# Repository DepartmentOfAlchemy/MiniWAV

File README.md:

# MiniWAV

The MiniWAV is a [FeatherWing](https://learn.adafruit.com/adafruit-feather/featherwings) designed for the [Feather](https://learn.adafruit.com/adafruit-feather) ecosystem create by [Adafruit](https://www.adafruit.com). It provides an SD card reader and I2S audio output to an 1/8" jack stereo audio line output. The board is designed to be used in a haunted attraction prop control system.

## Pinout
- I2S
  - BCK: A0
  - LRCK: A1
  - DIN: A2
- SD Card SPI
  - SCLK: SCK
  - DI: MO
  - DO: MI
  - CS: D10
  - DAT2: D9
  - DAT1: D6
  - CARDDET: D5

### SD Card
| Feather Pin | SPI     | SDIO    |
|-------------|---------|---------|
| SCK         | SCLK    | CLK     |
| MO          | SI      | CMD     |
| MI          | SO      | D0      |
| D10         | CS      | D3      |
| D9          | DAT2    | D2      |
| D6          | DAT1    | D1      |
| D5          | CARDDET | CARDDET |

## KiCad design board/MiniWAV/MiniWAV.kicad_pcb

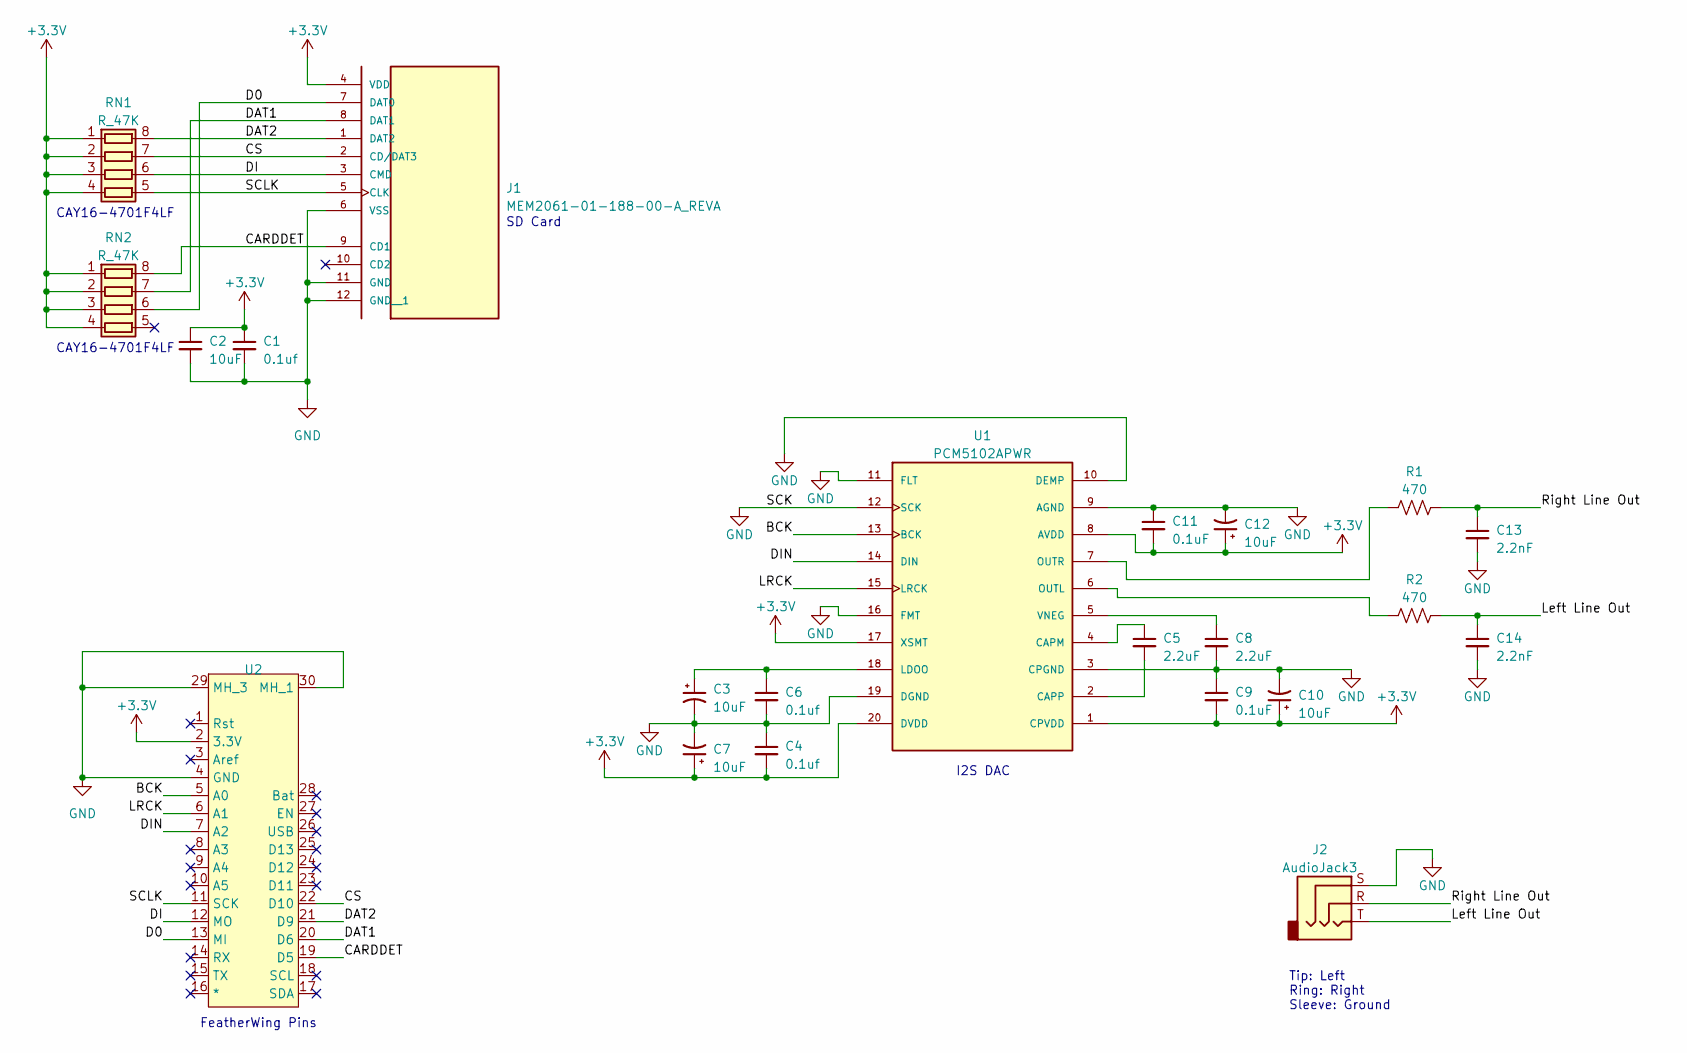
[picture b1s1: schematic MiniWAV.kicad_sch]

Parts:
C1, C4, C6: 0.1uf; C_0603_1608Metric
C2: 10uF; C_0603_1608Metric
C3, C7, C10, C12: 10uF; CAPPM2012X120N
C5, C8: 2.2uF; C_0603_1608Metric
C9, C11: 0.1uF; C_0603_1608Metric
C13, C14: 2.2nF; C_0603_1608Metric
J1: MEM2061-01-188-00-A_REVA; GCT_MEM2061-01-188-00-A_REVA
J2: AudioJack3; Jack_3.5mm_CUI_SJ-3523-SMT_Horizontal
R1, R2: 470; R_0603_1608Metric
RN1, RN2: R_47K; R_Array_Convex_4x0603
U1: PCM5102APWR; SOP65P640X120-20N; PARTREV C
U2: Feather Pins

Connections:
+3.3V: C1.1, C2.1, C4.2, C7.1, C9.2, C10.1, C11.2, C12.1, J1.4 (VDD), RN1.1 (R1.1), RN1.2 (R2.1), RN1.3 (R3.1), RN1.4 (R4.1), RN2.1 (R1.1), RN2.2 (R2.1), RN2.3 (R3.1), RN2.4 (R4.1), U1.1 (CPVDD), U1.8 (AVDD), U1.17 (XSMT), U1.20 (DVDD), U2.2 (3.3V)
/BCK: U1.13 (BCK), U2.5 (A0)
/CARDDET: J1.9 (CD1), RN2.8 (R1.2), U2.19 (D5)
/CS: J1.2 (CD/DAT3), RN1.7 (R2.2), U2.22 (D10)
/D0: J1.7 (DAT0), RN2.6 (R3.2), U2.13 (MI)
/DAT1: J1.8 (DAT1), RN2.7 (R2.2), U2.20 (D6)
/DAT2: J1.1 (DAT2), RN1.8 (R1.2), U2.21 (D9)
/DI: J1.3 (CMD), RN1.6 (R3.2), U2.12 (MO)
/DIN: U1.14 (DIN), U2.7 (A2)
/LRCK: U1.15 (LRCK), U2.6 (A1)
/Left Line Out: C14.1, J2.T, R2.2
/Right Line Out: C13.1, J2.R, R1.2
/SCLK: J1.5 (CLK), RN1.5 (R4.2), U2.11 (SCK)
GND: C1.2, C2.2, C3.2, C4.1, C6.2, C7.2, C8.2, C9.1, C10.2, C11.1, C12.2, C13.2, C14.2, J1.6 (VSS), J1.11 (GND), J1.12 (GND__1), J2.S, U1.3 (CPGND), U1.9 (AGND), U1.10 (DEMP), U1.11 (FLT), U1.12 (SCK), U1.16 (FMT), U1.19 (DGND), U2.4 (GND), U2.29 (MH_3), U2.30 (MH_1)
unnamed: C5.1, U1.4 (CAPM)
unnamed: C5.2, U1.2 (CAPP)
unnamed: C3.1, C6.1, U1.18 (LDOO)
unnamed: R2.1, U1.6 (OUTL)
unnamed: R1.1, U1.7 (OUTR)
unnamed: C8.1, U1.5 (VNEG)

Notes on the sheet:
SD Card
I2S DAC
FeatherWing Pins
CAY16-4701F4LF
Tip: Left Ring: Right Sleeve: Ground

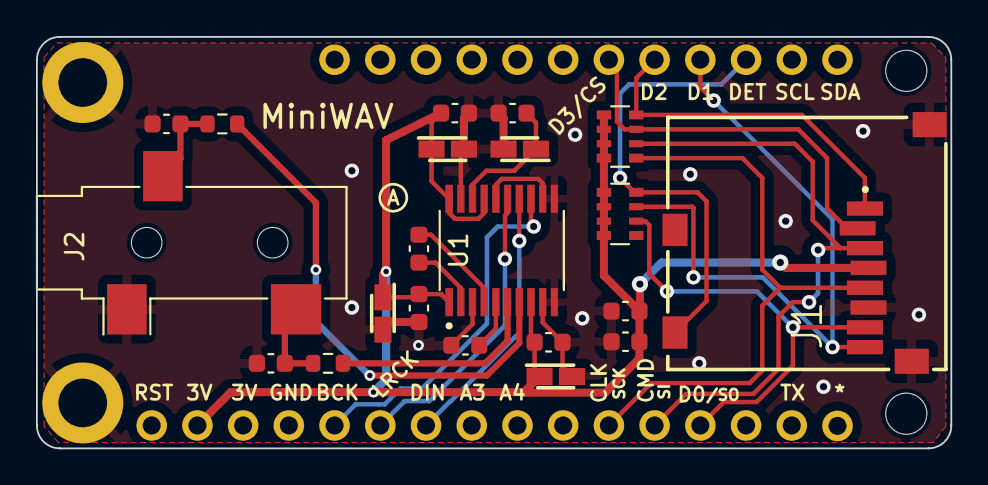
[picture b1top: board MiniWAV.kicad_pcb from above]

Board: 2 copper layers, 50.8 x 22.9 mm, 22 parts (0 on the bottom side), 20 nets.

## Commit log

2023-12-16 Initial commit.
2023-12-16 Update README.md
    Basic description of the board and pinout.
2024-07-14 Added the SD Card table to list both SPI and SDIO pins
